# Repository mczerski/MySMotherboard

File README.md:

# MySMotherboard
## Motherboard for MySensors nodes

This is a motherboard for creating MySensors nodes based on the atmega328p MCU. It is meant to be combined with a MySX daughter board to create fully functional MySensors node. It is primarly for battery powered nodes but can be also used as a gateway or ac powered node (ac power supply is not part of this project). It features multiple powering options and supports RS485 or RFM69 RF communication options. The size of the board is just a little bigger than a cr123a battery holder.

## Features:

1. atmega328p MCU
2. Multiple power source options:
  * CR123A battery or 16340 rechargable li-ion battery
  * CR2032 battery
  * JST-PH2 connector for rechargable li-ion battery
  * 24V on the 2.54mm screw terminal
  * VRAW from MySX connector
3. Multiple voltage regulator options:
  * MCP1640C boost converter with bypass option
  * TPS782 LDO linear regulator
  * AP63205WU buck converter
  * no voltage regulation - direct voltage from battery
4. Input voltage reverse polarity protection
5. Overvoltage protection for RS485 data lines
6. Battery voltage divider to monitor battery voltage
7. ATSHA204A supported
8. AT25DF512C flash suppoerted
9. RFM69 RF SMD module
10. RF module interrupt D2 pin can be disconnected if not used
11. SP3485 for RS485 communication
12. reset button
13. user button
14. user led
15. external oscillator for atmega

## HOW TO

### Minimum required parts to solder are:

1. MCU related parts:
C5, C6, C7, C10, IC5, R7
2. Radio module related parts:
C1, R1, RFM69W, antenna to ANT pad and R12 (R12 is just a 0Ohm jumper required to connect RFM69 interrupt with D2 pin)
3. RS485 interface related parts:
U8
3. MySX connector:
X2

This is bare minimum that is required to start with this board. In this configuration the board can be powered from the MySX connector VCC pin with voltage between 1.9V - 3.6V.

### Optional parts to solder are:

1. MCU related parts:
 * for user led - R8, D1
 * for reset button - RST
 * for user button connected to D2 pin - BTN
 * for I2C pull-up resistors - R9, R10
 * for external oscillator - C8, C9, Q2
2. External flash related parts:
R2, IC2
WARNING: flash chips consumes a lot of uA of current so it is not suited for battery powered nodes.
3. ATSHA204A related parts:
IC3
ATSHA204A requires at least 2.0V power supply
4. RS485 related parst (overvoltage protection on data pins):
F1, F2, D2, D3

### Powering options

The powering option is choosed in two steps. First is to select the voltage source, and second is to choose the voltage conversion type. Between the voltage source and the voltage converter ther is the reverse polarity protection mosfet Q1 which is required for all options and voltage divider for battery voltage monitoring which is not required.

Voltage source options are:
1. CR123A battery or 16340 rechargable li-ion battery. To select this option just solder CR123A battery holder.
2. CR2032 battery. To chosse this option just solder CR2032 battery holder.
3. JST-PH2 connector. To choose this option just solder the X1 connector.
4. 24V input on 2.54mm screw terminal
5. VRAW from MySX connector. To choose this option the J2 jumper must be shorted.

Reverse polarity battery protection:
Q1

Voltage divider for battery voltage monitoring:
R5, R6, C4

Voltage convertion options are:
1. MCP1640C boost converter
R3, R4, R11, C2, C3, L1, IC4, J1 jumper should connect VBOOST with VCC.
The MCP1640C boost converter can be put into bypass mode so it just passes the input voltage. It is controller by the A2 pin and the bypass mode is the default. The purpose of this functionality is to be able to run the MCU directly from the battery and to boost the voltage only for the moment required to make measurements with sensors that require higher voltages.
2. TPS782 LDO linear regulator
C13, C14, IC1. J1 jumper should connect VREG with VCC. The C12 should be replaced by the 0Ohm resistor. The C12 capacitor was designed for the APE8865 LDo which consumes much more current that TPS782.
3. AP63205WU buck converter
C1, C6, C11, U7, Q2 (for high voltage reverse polarity protection)
4. No voltage regulation
There is actually no direct way to shoose this option, but it can be done by shorting pins number 5 and 6 of the IC4 and J1 jumper should connect VBOOST with VCC.

### Powering examples.

1. Very low power temperature and humidity sensor based on the BME280 sensor.
This node uses the "No voltage conversion" option because the BME280 sensor can work with voltages as low as 1.2V. So the node may be powered just by 3V coin-cell battery. This type of node uses just CR2032 battery holder.

2. Very low power node with DS18B20 temperature sensors that require minimum 3V power supply.
This type of node uses MCP1640C boost converter to boost battery voltage for the measurement period. Use CR2032 battery holder and MCP1640C boost converter option. In the software controll properly the A2 pin to turn on/off boost conversion.

3. Motion sensor node.
Motion sensor such as AS312 consumes quite a lot of power and needs voltage between 2.7V and 3.3V. Powering it directly with 3V battery is not good, so we could use the boost converter. But boost converter makes to much noise for AS312 to work properly. The AS312 works the best with 3V LDO, so the power source should have higher voltage. The best options is to use 3.7V 16340 rechargable li-ion battery which fits into CR123A battery holder. Use TPS782 LDO option to power the MCU and RF module and short the J2 jumper to power the VRAW pin directly with 3.7V battery. Then the motion sensor daugher board should power the AS312 sensor with another LDO from the VRAW pin.

4. RS485 node.
RS485 node uses 24V input on the 2.54mm screw terminal which delivers power and RS485 communication to the board. It also utilises high voltage reverse polarity protection and overvoltage protection for data pins so any wiring mistakes will not cause damage to the board. Onboard AP63205WU buck converter provides 5V input voltage for the board which can be used directly or can be fed to the 3V LDO regulator. By soldering JP1 jumper 5V power can be connected to VRAW on the MySX connector.

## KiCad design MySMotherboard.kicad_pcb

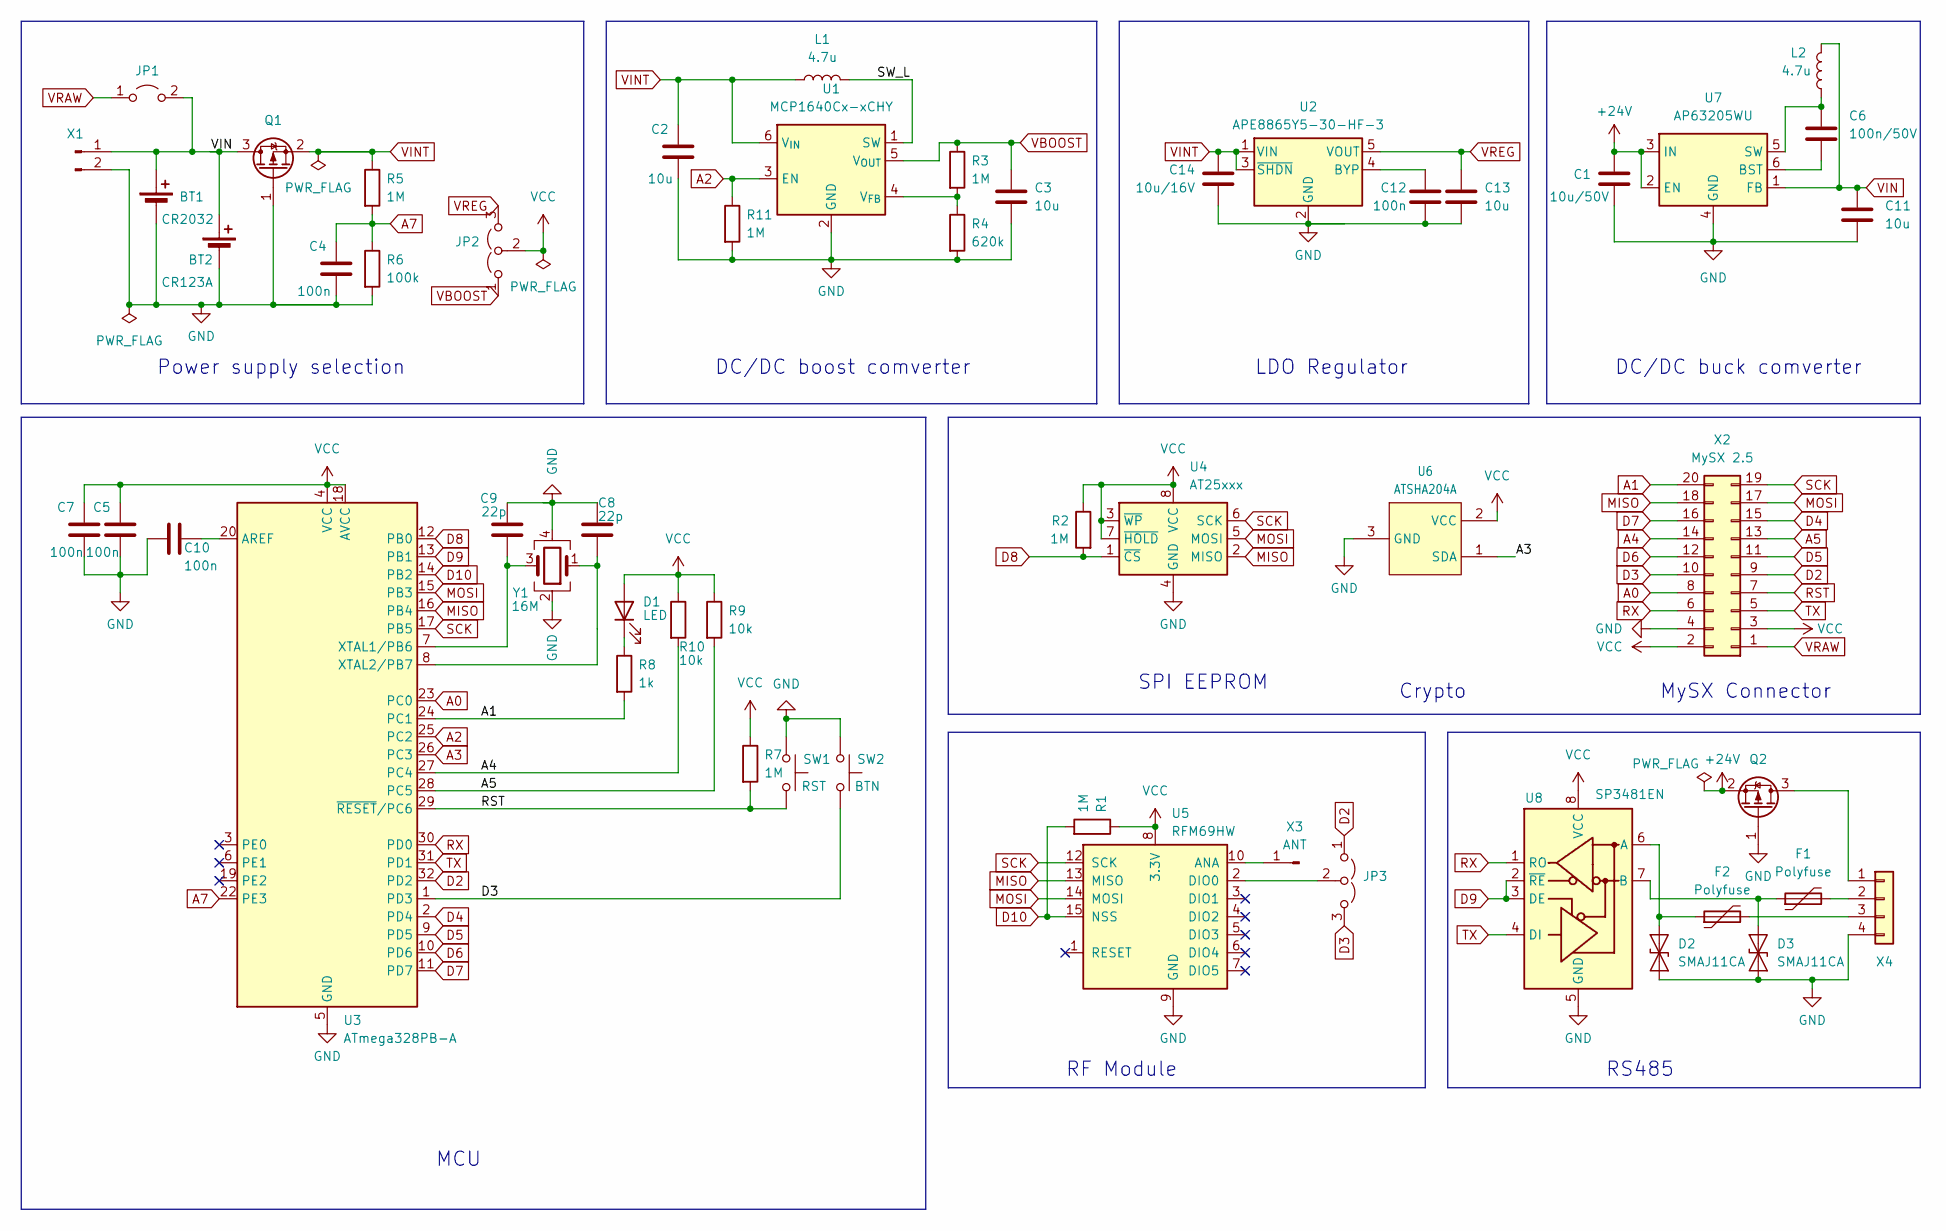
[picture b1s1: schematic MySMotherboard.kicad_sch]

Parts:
BT1: CR2032; BatteryHolder_Keystone_1060_1x2032
BT2: CR123A; BH123A
C1: 10u/50V; C_1206_3216Metric
C2, C3, C13: 10u; C_0603_1608Metric
C4, C5, C7, C10, C12: 100n; C_0402_1005Metric
C6: 100n/50V; C_0402_1005Metric_Pad0.74x0.62mm_HandSolder
C8, C9: 22p; C_0402_1005Metric
C11: 10u; C_1206_3216Metric
C14: 10u/16V; C_0603_1608Metric
D1: LED; LED_0805_2012Metric_Pad1.15x1.40mm_HandSolder
D2, D3: SMAJ11CA; D_SMA
F1, F2: Polyfuse; Fuse_1206_3216Metric_Pad1.42x1.75mm_HandSolder
JP1: SolderJumper-2_P1.3mm_Open_RoundedPad1.0x1.5mm
JP2, JP3: SolderJumper-3_P1.3mm_Open_RoundedPad1.0x1.5mm
L1: 4.7u; L_1210_3225Metric_Pad1.42x2.65mm_HandSolder
L2: 4.7u; L_1210_3225Metric
Q1, Q2: SOT-23
R1, R2, R3, R5, R7, R11: 1M; R_0603_1608Metric
R4: 620k; R_0603_1608Metric
R6: 100k; R_0603_1608Metric
R8: 1k; R_0603_1608Metric
R9, R10: 10k; R_0603_1608Metric
SW1: RST; SW_SPST_EVQPE1
SW2: BTN; SW_SPST_EVQPE1
U1: MCP1640Cx-xCHY; SOT-23-6
U2: APE8865Y5-30-HF-3; SOT-23-5
U3: ATmega328PB-A; TQFP-32_7x7mm_P0.8mm
U4: AT25xxx; SOIC-8_3.9x4.9mm_P1.27mm
U5: RFM69HW; HOPERF_RFM69HW
U6: ATSHA204A; SOT-23
U7: AP63205WU; TSOT-23-6
U8: SP3481EN; SOIC-8_3.9x4.9mm_P1.27mm
X1: JST_PH_B2B-PH-K_1x02_P2.00mm_Vertical
X2: MySX 2.5; PinHeader_2x10_P2.54mm_Vertical
X3: ANT; PinHeader_1x01_P2.54mm_Vertical
X4: TerminalBlock_Phoenix_MPT-0,5-4-2.54_1x04_P2.54mm_Horizontal
Y1: 16M; Crystal_SMD_2520-4Pin_2.5x2.0mm

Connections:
+24V: C1.1, Q2.2 (S), U7.2 (EN), U7.3 (IN)
/SW_L: L1.2, U1.1 (SW)
A0: U3.23 (PC0), X2.8
A1: R8.2, U3.24 (PC1), X2.20
A2: R11.1, U1.3 (EN), U3.25 (PC2)
A3: U3.26 (PC3), U6.1 (SDA)
A4: R10.2, U3.27 (PC4), X2.14
A5: R9.2, U3.28 (PC5), X2.13
A7: C4.1, R5.2, R6.1, U3.22 (PE3)
D2: JP3.1 (A), U3.32 (PD2), X2.9
D3: JP3.3 (B), SW2.1, U3.1 (PD3), X2.10
D4: U3.2 (PD4), X2.15
D5: U3.9 (PD5), X2.11
D6: U3.10 (PD6), X2.12
D7: U3.11 (PD7), X2.16
D8: R2.2, U3.12 (PB0), U4.1 (~CS)
D9: U3.13 (PB1), U8.2 (~RE), U8.3 (DE)
D10: R1.2, U3.14 (PB2), U5.15 (NSS)
GND: BT1.2 (-), BT2.2 (-), C1.2, C2.2, C3.2, C4.2, C5.2, C7.2, C8.1, C9.2, C10.2, C11.2, C12.2, C13.2, C14.2, D2.1 (A1), D3.1 (A1), Q1.1 (G), Q2.1 (G), R4.2, R6.2, R11.2, SW1.2, SW2.2, U1.2 (GND), U2.2 (GND), U3.5 (GND), U3.21 (GND), U4.4 (GND), U5.9 (GND), U5.11 (GND), U6.3 (GND), U7.4 (GND), U8.5 (GND), X1.2, X2.4, X4.4, Y1.2, Y1.4
MISO: U3.16 (PB4), U4.2 (MISO), U5.13 (MISO), X2.18
MOSI: U3.15 (PB3), U4.5 (MOSI), U5.14 (MOSI), X2.17
unnamed: D1.1 (K), R8.1
unnamed: D2.2 (A2), F2.1, U8.6 (A)
unnamed: D3.2 (A2), F1.1, U8.7 (B)
unnamed: JP3.2 (C), U5.2 (DIO0)
unnamed: Q2.3 (D), X4.1
unnamed: R3.2, R4.1, U1.4 (V_{FB})
unnamed: C12.1, U2.4 (BYP)
unnamed: C10.1, U3.20 (AREF)
unnamed: C9.1, U3.7 (XTAL1/PB6), Y1.3
unnamed: C8.2, U3.8 (XTAL2/PB7), Y1.1
unnamed: U5.10 (ANA), X3.1
unnamed: C6.1, U7.6 (BST)
unnamed: C6.2, L2.1, U7.5 (SW)
unnamed: F1.2, X4.2
unnamed: F2.2, X4.3
RST: R7.2, SW1.1, U3.29 (~RESET/PC6), X2.7
RX: U3.30 (PD0), U8.1 (RO), X2.6
SCK: U3.17 (PB5), U4.6 (SCK), U5.12 (SCK), X2.19
TX: U3.31 (PD1), U8.4 (DI), X2.5
VBOOST: C3.1, JP2.1 (A), R3.1, U1.5 (V_{OUT})
VCC: C5.1, C7.1, D1.2 (A), JP2.2 (C), R1.1, R2.1, R7.1, R9.1, R10.1, U3.4 (VCC), U3.18 (AVCC), U4.3 (~WP), U4.7 (~HOLD), U4.8 (VCC), U5.8 (3.3V), U6.2 (VCC), U8.8 (VCC), X2.2, X2.3
VIN: BT1.1 (+), BT2.1 (+), C11.1, JP1.2 (B), L2.2, Q1.3 (D), U7.1 (FB), X1.1
VINT: C2.1, C14.1, L1.1, Q1.2 (S), R5.1, U1.6 (V_{IN}), U2.1 (VIN), U2.3 (~SHDN)
VRAW: JP1.1 (A), X2.1
VREG: C13.1, JP2.3 (B), U2.5 (VOUT)

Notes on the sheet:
RS485
LDO Regulator
DC/DC boost comverter
RF Module
Crypto
MySX Connector
MCU
SPI EEPROM
DC/DC buck comverter
Power supply selection

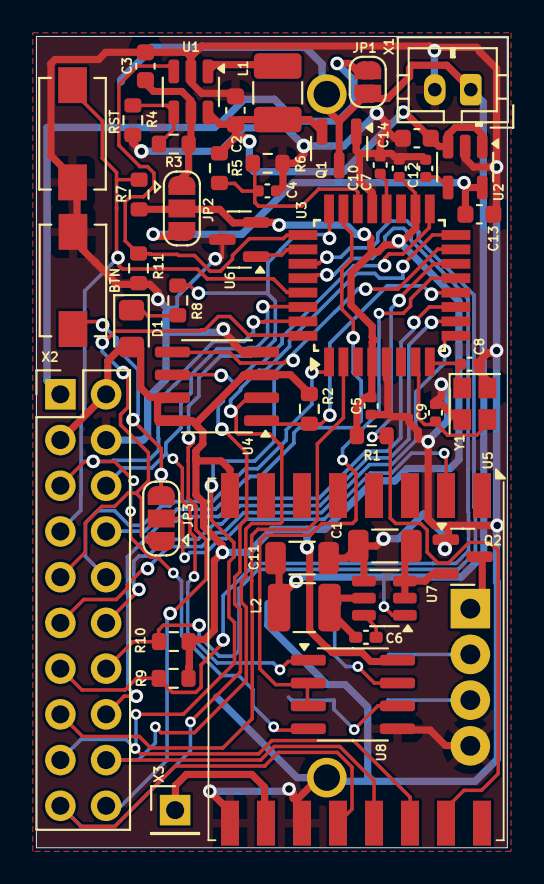
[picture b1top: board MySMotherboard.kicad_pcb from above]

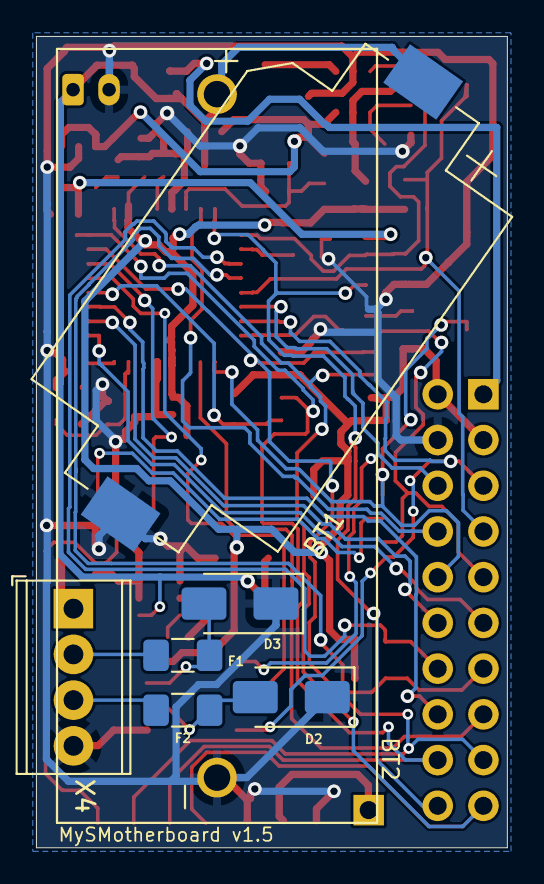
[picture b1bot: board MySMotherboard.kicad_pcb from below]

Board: 2 copper layers, 26.2 x 45.1 mm, 54 parts (7 on the bottom side), 46 nets.

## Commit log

2017-10-14 initial commit - raw version, just schematic and pcb layout
2017-12-07 1. fix wrong boost converter footprint 2. connect led to A1 pin instead of A2 (which was used by the boost converter enable 3. change crystal footrint but not change the pcb
2017-12-07 1. rearrange nfr24l01 connector and atmega328p chip
2018-02-08 connect radio module irq with d2
2018-05-15 use p-mosfet for reverse polarity
2018-05-17 add RFM69
2018-06-10 remove eagle.epf from repo
2018-06-10 add 0Ohm resistor for radio module interrupt + connect button to D3
2018-06-10 move ldo to top layer
2018-06-10 rotate cr2032 battery pack to about 55 degrees
2018-07-22 rename files
2018-07-22 add pictures
2018-07-22 add documentation files
2018-07-22 add new foto
2018-07-23 add license documentation
2018-07-23 update gerbers after adding license notice
2024-05-20 convert to KiCad
2024-05-22 refactor schematic to use native KiCad symbols and footprints
2024-05-25 replace NRF24L01 with RS485 inteface
2024-06-07 change bypass capacitor for buck dc/dc converter to 50V 0603
2024-06-07 add protection circuitry for RS485 IC AB lines
2024-06-07 add reverse polarity protection for 24V input
2024-06-08 update PCB with latest changes
2024-06-08 update README and schematic pdf export
2024-06-08 update gerber files
2024-06-08 change 22uF cap on buck converter output to 10uF
    10uF should be sufficient
2024-06-08 change bypass capacitor for buck converter from 0603 to 0402
2024-07-24 update parts documentation sources
2025-01-03 update to kicad 8
2025-10-19 add pull-up resistor for RFM69W NSS pin
2025-10-19 add option to connect RFM69W irq to pin 3
2025-10-19 update production files
